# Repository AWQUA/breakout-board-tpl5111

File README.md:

# breakout-board-tpl5111

The TPL5111 is a power-gating chip, meant to sit between a power source and a piece of circuitry -- for example a microcontroller -- and periodically cycle power on and off. The TPL5111 consumes only tens of nanoamperes while performing this feat, making it more power-conscious than the lowest deep-sleep setting of many microcontrollers, and a great addition to the design of low-power, long-term environmental monitoring devices. 

The duration of the power cycle is a fixed interval controlled by a resistance applied between ground and the chip's DELAY pin, which may be too limiting for some monitoring devices that need highly dynamic sampling intervals. The delay interval can be set to 0 (always on) by shorting the DELAY pin to the positive rail. Best of all, the chip has a pin (DONE) for receiving a signal that the operation your device was awakened to do has completed and power may be safely turned off.

Datasheet: http://www.ti.com/lit/ds/symlink/tpl5111.pdf

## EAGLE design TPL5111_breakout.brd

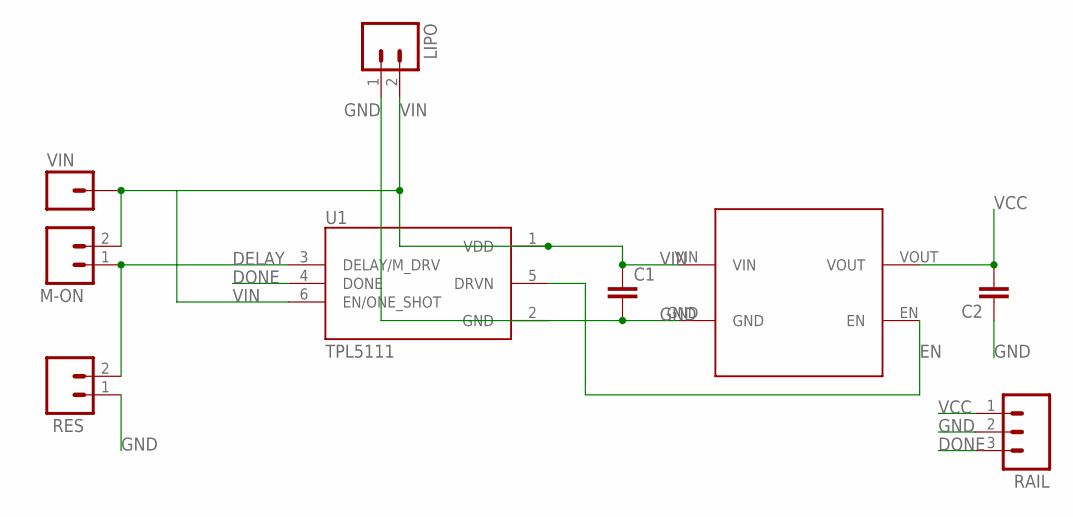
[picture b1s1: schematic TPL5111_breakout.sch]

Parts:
C1, C2: CAP0603-CAP; 0603-CAP
LIPO: M02PTH; 1X02
M-ON: M02PTH; 1X02
RAIL: M03PTH; 1X03
RES: M02PTH; 1X02
U1: TPL5111; SOT95P280X110-6N
U$2: AP2112K; AP2112K-SOT23-5
VIN: M01PTH; 1X01

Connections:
DELAY: M-ON.1, RES.2, U1.3 (DELAY/M_DRV)
DONE: RAIL.3, U1.4 (DONE)
EN: U1.5 (DRVN), U$2.EN
GND: C1.2, C2.1, LIPO.1, RAIL.2, RES.1, U1.2 (GND), U$2.GND
VCC: C2.2, RAIL.1, U$2.VOUT
VIN: C1.1, LIPO.2, M-ON.2, U1.1 (VDD), U1.6 (EN/ONE_SHOT), U$2.VIN, VIN.1

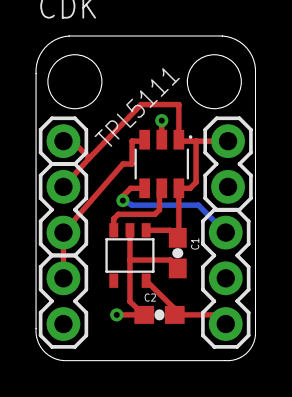
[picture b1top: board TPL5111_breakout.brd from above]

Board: 2 copper layers, 12.2 x 18.0 mm, 9 parts (0 on the bottom side), 6 nets.

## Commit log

2017-03-08 board added

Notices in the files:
parts and their libraries:
SparkFun-Connectors: Licensing: Creative Commons ShareAlike 4.0 International - https://creativecommons.org/licenses/by-sa/4.0
